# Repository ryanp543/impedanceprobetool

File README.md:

# Impedance Probe Tool Intermediary Board

## Overview

This repository contains the intermediary board between the Teensy LC and Digilent Pmod-IA (Impedance Analyzer) boards used in the impedance analyzer probe tool, which is one of the instruments developed for operation by the MIT Bioinstrumentation Lab rover. The Autodesk Eagle layout and schematics can be found in the `Impedance Analyzer` directory. 

The two probes are connected to a Digilent Pmod-IA board, part of Digilent's line of small input-output interface boards. This Digilent Board is then connect to the custom-made intermediary board with the necessary electrical components to communicate with a Teensy LC over I2C protocol lines. All of these boards are packaged into a container built with a 3D printer and laser cutter.

The Teensy simply receives commands from the TOSLink transceiver and operates the Digilent Pmod-IA by sending the appropriate bit commands over the I2C lines. The high level commands simply determine the reference resistor. For instance, measuring a resistance range of 100 Ohm to 10 kOhm requires the use of a certain reference resistor, so the proper settings are adjusted on the Pmod-IA. However, on a lower level, the voltage range, number of samples, frequency sweep, and gain amplifier are all programmable from the control box without having to change the firmware on the Teensy.

## Contributors

#### Primary Contributors
Ryan Poon from the [MIT Bioinstrumentation Lab](https://bioinstrumentation.mit.edu/) is the primary contributor of this project.

#### Other Contributors
Professor Ian Hunter served as the main advisor.

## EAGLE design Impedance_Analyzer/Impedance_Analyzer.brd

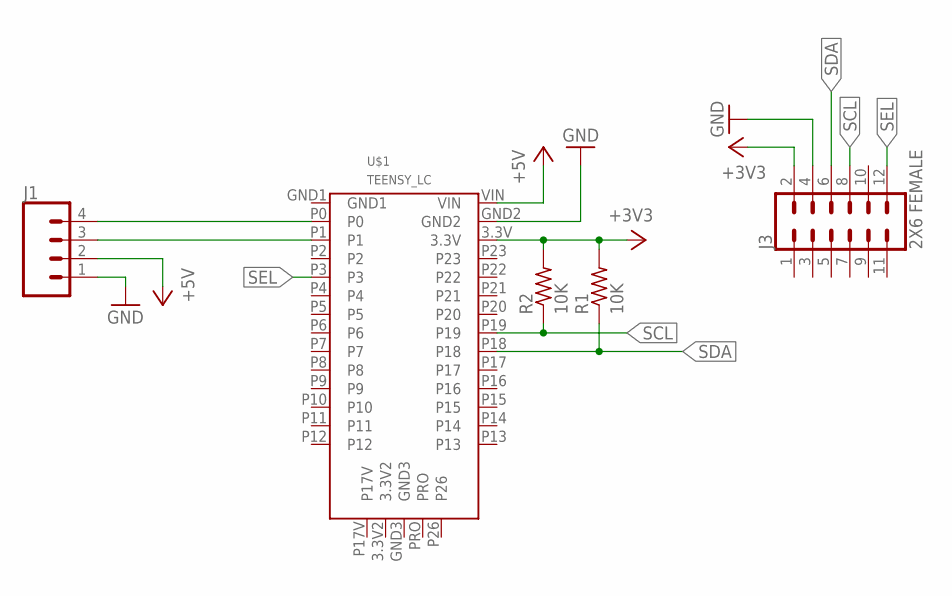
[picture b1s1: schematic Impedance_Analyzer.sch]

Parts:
J1: CONN_04; 1X04
J3: 2X6 FEMALE; 2X6
R1, R2: 10K; 0204/5
U$1: TEENSY_LC

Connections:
+3V3: J3.2, R1.2, R2.2, U$1.3.3V
+5V: J1.2, U$1.VIN
GND: J1.1, J3.4, U$1.GND2
RX: J1.4, U$1.P0
SCL: J3.8, R2.1, U$1.P19
SDA: J3.6, R1.1, U$1.P18
SEL: J3.12, U$1.P3
TX: J1.3, U$1.P1

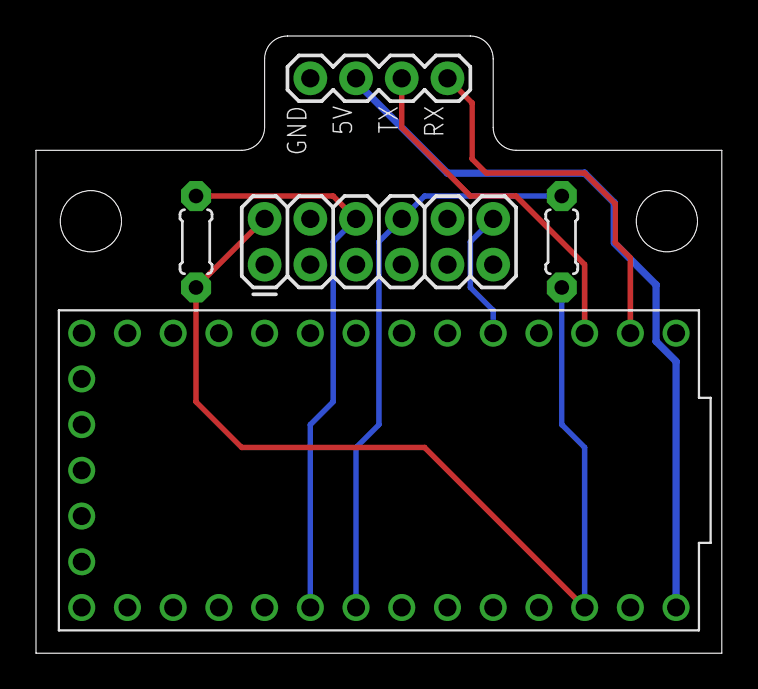
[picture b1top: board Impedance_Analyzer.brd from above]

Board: 2 copper layers, 38.1 x 34.3 mm, 5 parts (0 on the bottom side), 8 nets.

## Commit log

2021-05-03 first update

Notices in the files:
parts and their libraries:
SparkFun-Connectors: Licensing: Creative Commons ShareAlike 4.0 International - https://creativecommons.org/licenses/by-sa/4.0
